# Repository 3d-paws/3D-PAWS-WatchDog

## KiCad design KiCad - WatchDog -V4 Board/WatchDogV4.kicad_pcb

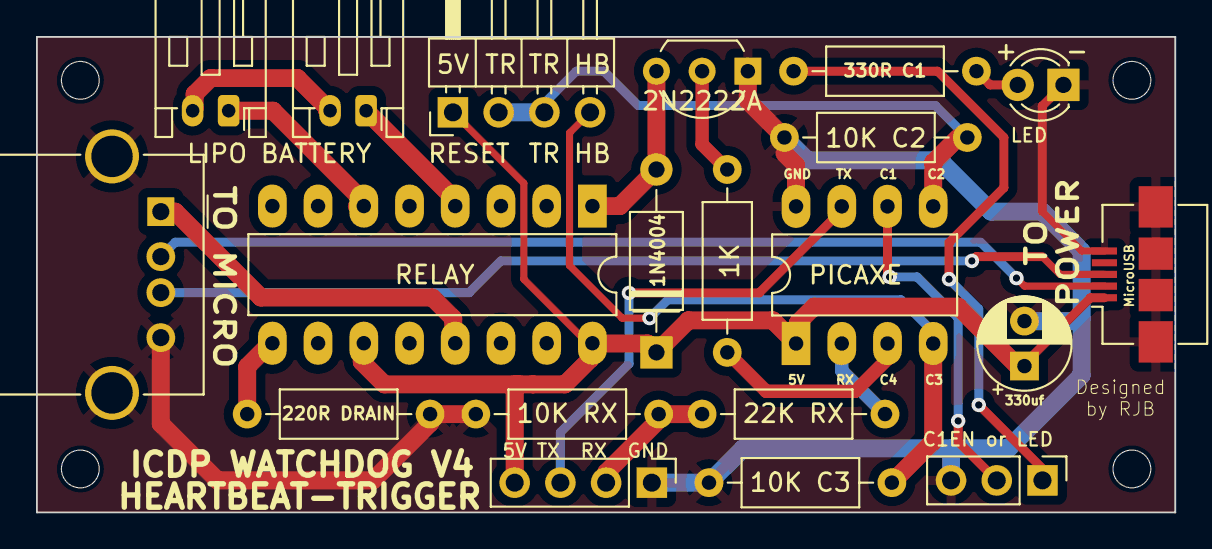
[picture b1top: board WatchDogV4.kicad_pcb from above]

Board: 2 copper layers, 63.2 x 26.4 mm, 21 parts (0 on the bottom side), 9 nets.

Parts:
1K, 10K C2, 10K C3, 10K RX, 22K RX, 220R DRAIN, 330R C1: R_Axial_DIN0207_L6.3mm_D2.5mm_P10.16mm_Horizontal
1N4004: D_A-405_P10.16mm_Horizontal
2N2222A: TO-92L_Inline_Wide
330uf: CP_Radial_D5.0mm_P2.50mm
BAT IN: JST_PH_S2B-PH-K_1x02_P2.00mm_Horizontal
BAT-OUT: JST_PH_S2B-PH-K_1x02_P2.00mm_Horizontal
BLH: MountingHole_2.1mm
BRH: MountingHole_2.1mm
LED: LED_D3.0mm
MicroUSB: USB_Micro-B_Amphenol_10104110_Horizontal
PICAXE: DIP-8_W7.62mm_LongPads
RELAY: DIP-16_W7.62mm_LongPads
TLH: MountingHole_2.1mm
TO MICRO: USB_A_Molex_67643_Horizontal
TRH: MountingHole_2.1mm

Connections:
5V: 1N4004.1, 330uf.1, MicroUSB.1, PICAXE.1, RELAY.11, RELAY.16
Base: 1K.2, 2N2222A.2
Collector: 1N4004.2, 2N2222A.3, RELAY.1
D+: MicroUSB.3, TO MICRO.3
D-: MicroUSB.2, TO MICRO.2
GND: 2N2222A.1, 10K C2.1, 10K C3.1, 10K RX.1, 220R DRAIN.1, 330uf.2, LED.1, MicroUSB.5, MicroUSB.6, PICAXE.8, TO MICRO.4, TO MICRO.5
HB: 10K C3.2, PICAXE.4
RX: 10K RX.2, 22K RX.1
TR: 10K C2.2, PICAXE.5, RELAY.4

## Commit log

2024-07-15 Initial
2024-07-15 Remove
2024-08-21 Delete
2025-05-28 OpenSCAD - Enclousure
